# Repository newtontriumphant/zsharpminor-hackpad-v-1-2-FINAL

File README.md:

# zsharpminor-hackpad-v-1-2-FINAL

HackPad built by zsharpminor for HackClub's Blueprint Program. Fully Modular, with 6 Cherry MX-Style Switch Ports, 1 Rotary Encoder, and 1 Mini RGB LED.

Fun Fact: This was my first time creating a serious project in KiCad! I think it turned out quite well, took some time but it was worth it! Hopefully it works :)

**UPDATE**: Gerber file ZIP added to PCB folder.

BOM CSV FILE: https://docs.google.com/spreadsheets/d/1cF9aBQvLo8gZvru_nWJd0H63MU4cm--T6njjNDXQBQc

(BOM and placement CSV files also placed inside the PCB folder for easy access).

# BOM:

* 1x PCB
* 1x Seeed XIAO RP2040 Through-Hole
* 6x Cherry MX-style Switches
* 6x Cherry MX-style Keycaps (Blank)
* 1x EC11 Rotary Encoder
* 1x SK6812 MINI-E LED
* 4x M3x16mm screws
* 4x M3x5mx4mm heatset inserts

* 1x Case to be entirely 3d-printed (self-provided), iterations may occur.

# UPDATE: CAD MODEL WITH 3D MODELED PCB AND COMPONENTS!

## No. 1: PCB in case without keycaps:

## No. 2: PCB in case with keycaps:

## No. 3: FULLY ASSEMBLED case with PCB in a mock-up of red PLA.

(Ignore the silly keycap profile, also I couldn't find an exact texture for the rotary encoder knob I have so I hope it doesn't get denied for that!)

# Finalized HackPad Mockup:

# Case Parts:

# Schematic:

# PCB:

# PCB 3d Render:

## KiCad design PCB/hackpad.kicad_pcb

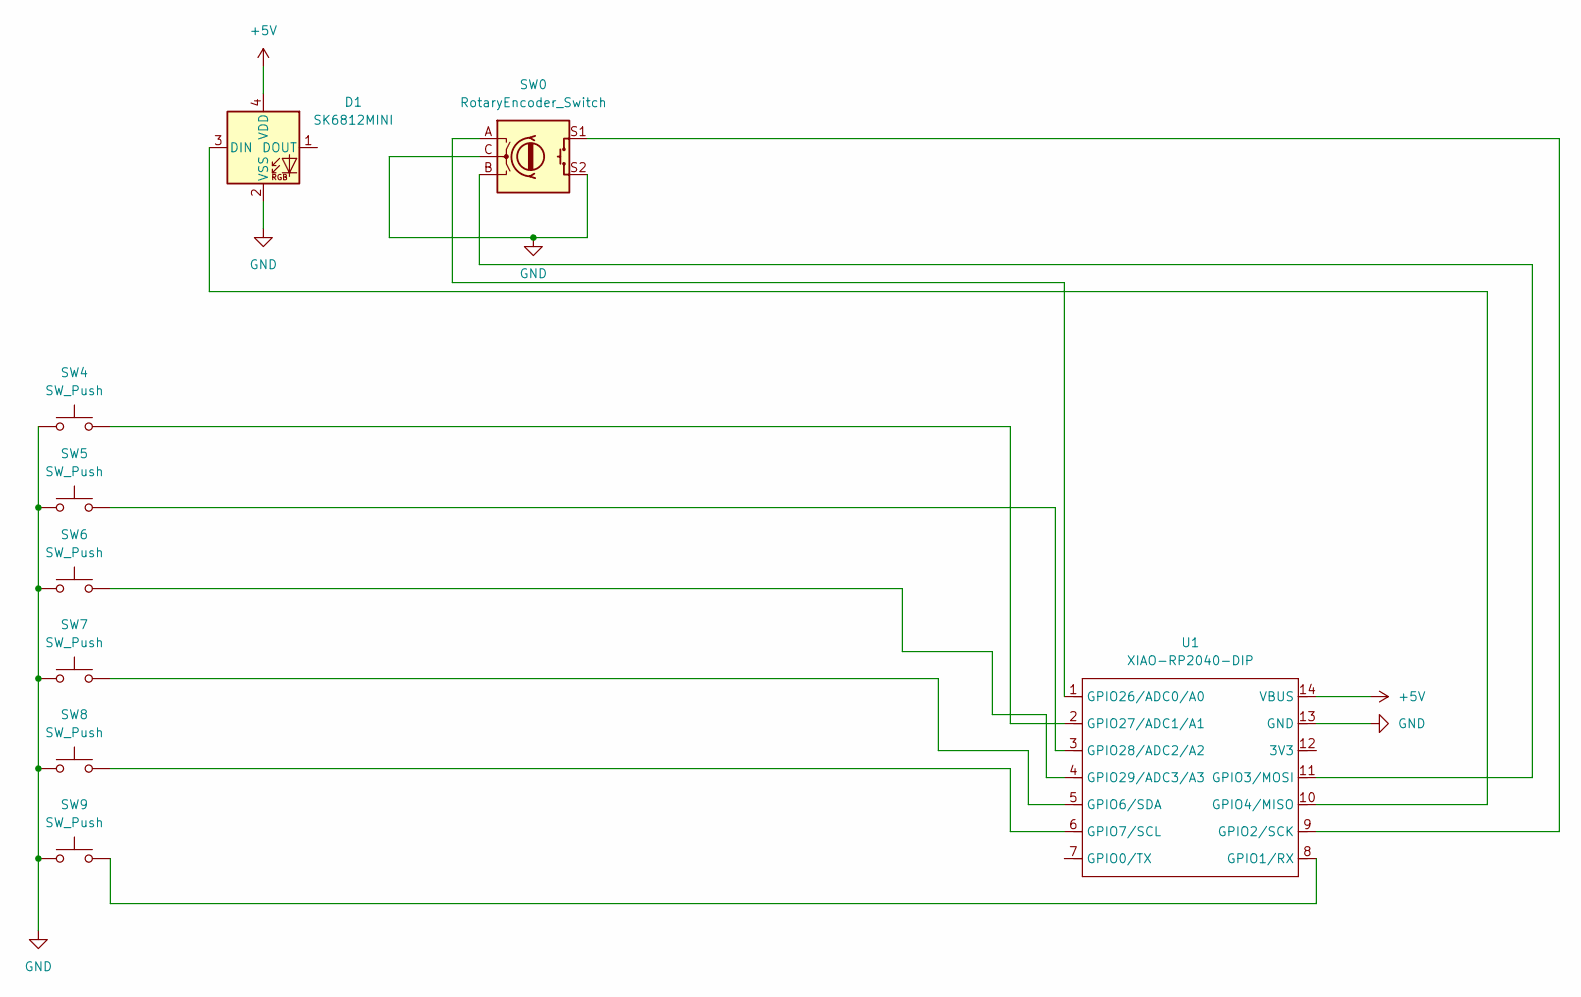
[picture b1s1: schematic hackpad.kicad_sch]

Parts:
D1: SK6812MINI; LED_SK6812MINI_PLCC4_3.5x3.5mm_P1.75mm
SW0: RotaryEncoder_Switch; RotaryEncoder_Alps_EC11E-Switch_Vertical_H20mm
SW4, SW5, SW6, SW7, SW8, SW9: SW_Push; SW_Cherry_MX_1.00u_PCB
U1: XIAO-RP2040-DIP

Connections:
+5V: D1.4 (VDD), U1.14 (VBUS)
GND: D1.2 (VSS), SW0.C, SW0.S2, SW4.1, SW5.1, SW6.1, SW7.1, SW8.1, SW9.1, U1.13 (GND)
unnamed: D1.3 (DIN), U1.10 (GPIO4/MISO)
unnamed: SW9.2, U1.8 (GPIO1/RX)
unnamed: SW0.S1, U1.9 (GPIO2/SCK)
unnamed: SW0.B, U1.11 (GPIO3/MOSI)
unnamed: SW7.2, U1.5 (GPIO6/SDA)
unnamed: SW8.2, U1.6 (GPIO7/SCL)
unnamed: SW0.A, U1.1 (GPIO26/ADC0/A0)
unnamed: SW4.2, U1.2 (GPIO27/ADC1/A1)
unnamed: SW5.2, U1.3 (GPIO28/ADC2/A2)
unnamed: SW6.2, U1.4 (GPIO29/ADC3/A3)

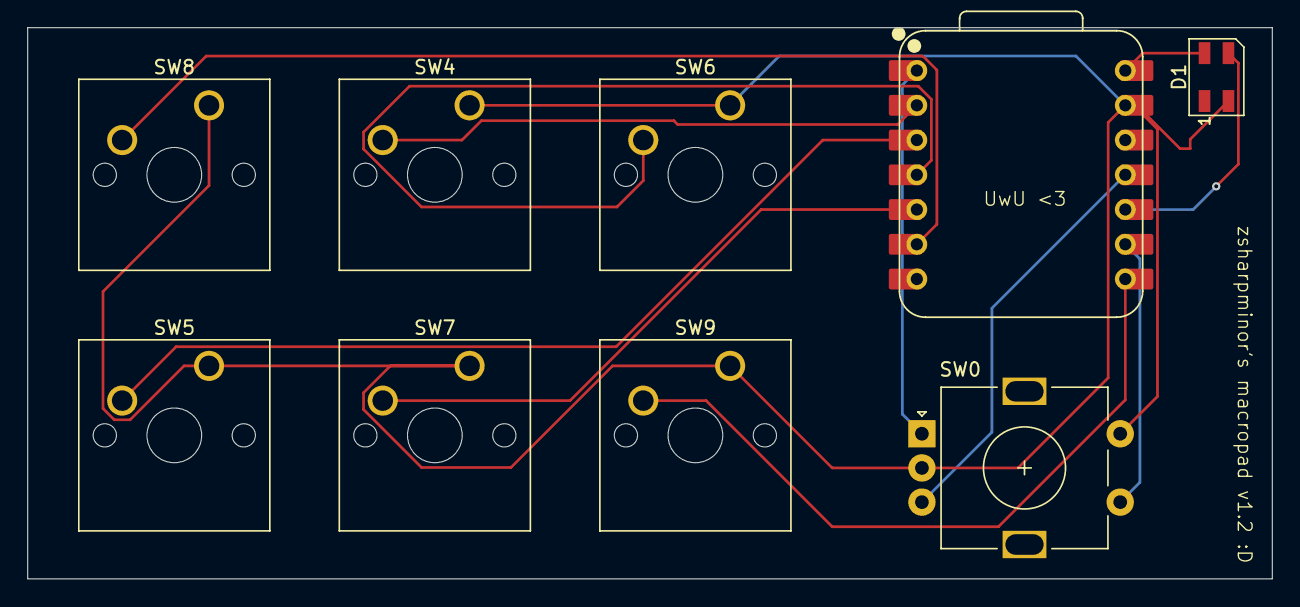
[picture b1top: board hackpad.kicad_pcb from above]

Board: 2 copper layers, 91.0 x 40.3 mm, 9 parts (0 on the bottom side), 12 nets.

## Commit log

2025-11-30 Add Main Files.
2025-11-30 Updated README with correct Rotary Encoder and More Screenshots!
2025-11-30 Changed Rotary Encoder from MP to non-MP
2025-12-01 FINALIZED Readme with proper depiction of Electronic Components.
2025-12-01 FINAL SUBMISSION FILE
2025-12-02 Added Gerbers
2025-12-02 Updated README with BOM link
2025-12-02 Added Self-Made BOM
2025-12-02 Added BOM and POS files (two formats).
2025-12-02 Rename zsharpminor-hackpad-bom-kicad-auto-generated.csv to bom-autogenerated
2025-12-02 Rename bom-autogenerated to BOM-autogenerated.csv
